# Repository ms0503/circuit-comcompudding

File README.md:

ComComPudding
=============

ComComPuddingは「通信」を主軸に設計された汎用基板です。
MCUはSTM32F405RGT6を採用しコンパクトながら素早く処理することができます。

# 使用IC
## MCP2542WFD
高速通信可能なCANトランシーバです。
詳細は[データシート](https://ww1.microchip.com/downloads/aemDocuments/documents/APID/ProductDocuments/DataSheets/MCP2542FD-MCP2542WFD-4WFD-Data-Sheet-DS20005514C.pdf)
をご覧下さい。

## STM32F405RGT6
メインの処理を担当するMCUです。
詳細は[データシート](https://www.st.com/resource/en/datasheet/stm32f405rg.pdf)
及び[リファレンスマニュアル](https://www.stmcu.jp/download/?dlid=51544_jp)
をご覧下さい。

# インターフェース
## CAN
CAN(Control Area Network)向けのポートが1系統、2つ搭載されており、CANへのアクセス、
5V電源の供給を行うことが出来ます。
### 信号レベル
- マイコン側：3.3V
- 端子側：5V

### マイコンピン
TX：PA11
RX：PA12

## I²C
I²C(Inter-Intergrated Circuit)向けのポートが1系統、1つ搭載されており、I²Cへのアクセス、
5V電源の供給を行うことが出来ます。
### 信号レベル
3.3V
### マイコンピン
I2C1\_SCL：PB6
I2C1\_SDA：PB7

## LED
基板表面に実装された4つのLEDで簡易的な状態表示を行うことが出来ます。
### 信号レベル
3.3V
### マイコンピン
LED1：PB12
LED2：PB13
LED3：PB14
LED4：PB15

## SPI
SPI(Serial Peripheral Interface)向けのポートが2系統、3つ搭載されており、SlaveとしてのMasterとの通信、
MasterとしてのSlave(最大2台まで)との通信、5V電源の供給を行うことが出来ます。  
SPI1をSlave動作、SPI2をMaster動作とすることを想定しています。
### 信号レベル
3.3V
### マイコンピン
SPI1\_SCK：PA5
SPI1\_MISO：PA6
SPI1\_MOSI：PA7
SPI1\_SS：PA4
SPI2\_SCK：PB10
SPI2\_MISO：PC2
SPI2\_MOSI：PC3
SPI2\_SS\_1：PC0
SPI2\_SS\_2：PC1

## U(S)ART
USART(Universal Synchronous-Asynchronous Receiver and Transmitter)向けのポートが4つ、
UART(Universal Asynchronous Receiver and Transmitter)向けのポートが2つ、計6つ搭載されており、
U(S)ARTデバイスとの通信、5V電源の供給を行うことが出来ます。
### 信号レベル
3.3V
### マイコンピン
USART1\_TX：PA9
USART1\_RX：PA10
USART2\_TX：PA2
USART2\_RX：PA3
USART3\_TX：PC10
USART3\_RX：PB11
UART4\_TX：PA0
UART4\_RX：PA1
UART5\_TX：PC12
UART5\_RX：PD2
USART6\_TX：PC6
USART6\_RX：PC7

# ライブラリ
この基板は一部のシンボル・フットプリントに[kicad-mecha](https://github.com/ms0503/kicad-mecha.git)を使用しています。
別途インポートした上でご利用下さい。

# 設計者
Sora Tonami <[ms0503@outlook.com](mailto:ms0503@outlook.com)>

# ライセンス
この基板のデータは[MITライセンス](LICENSE.md)の下に公開されます。ご自由に改変・再配布して頂いて構いません。

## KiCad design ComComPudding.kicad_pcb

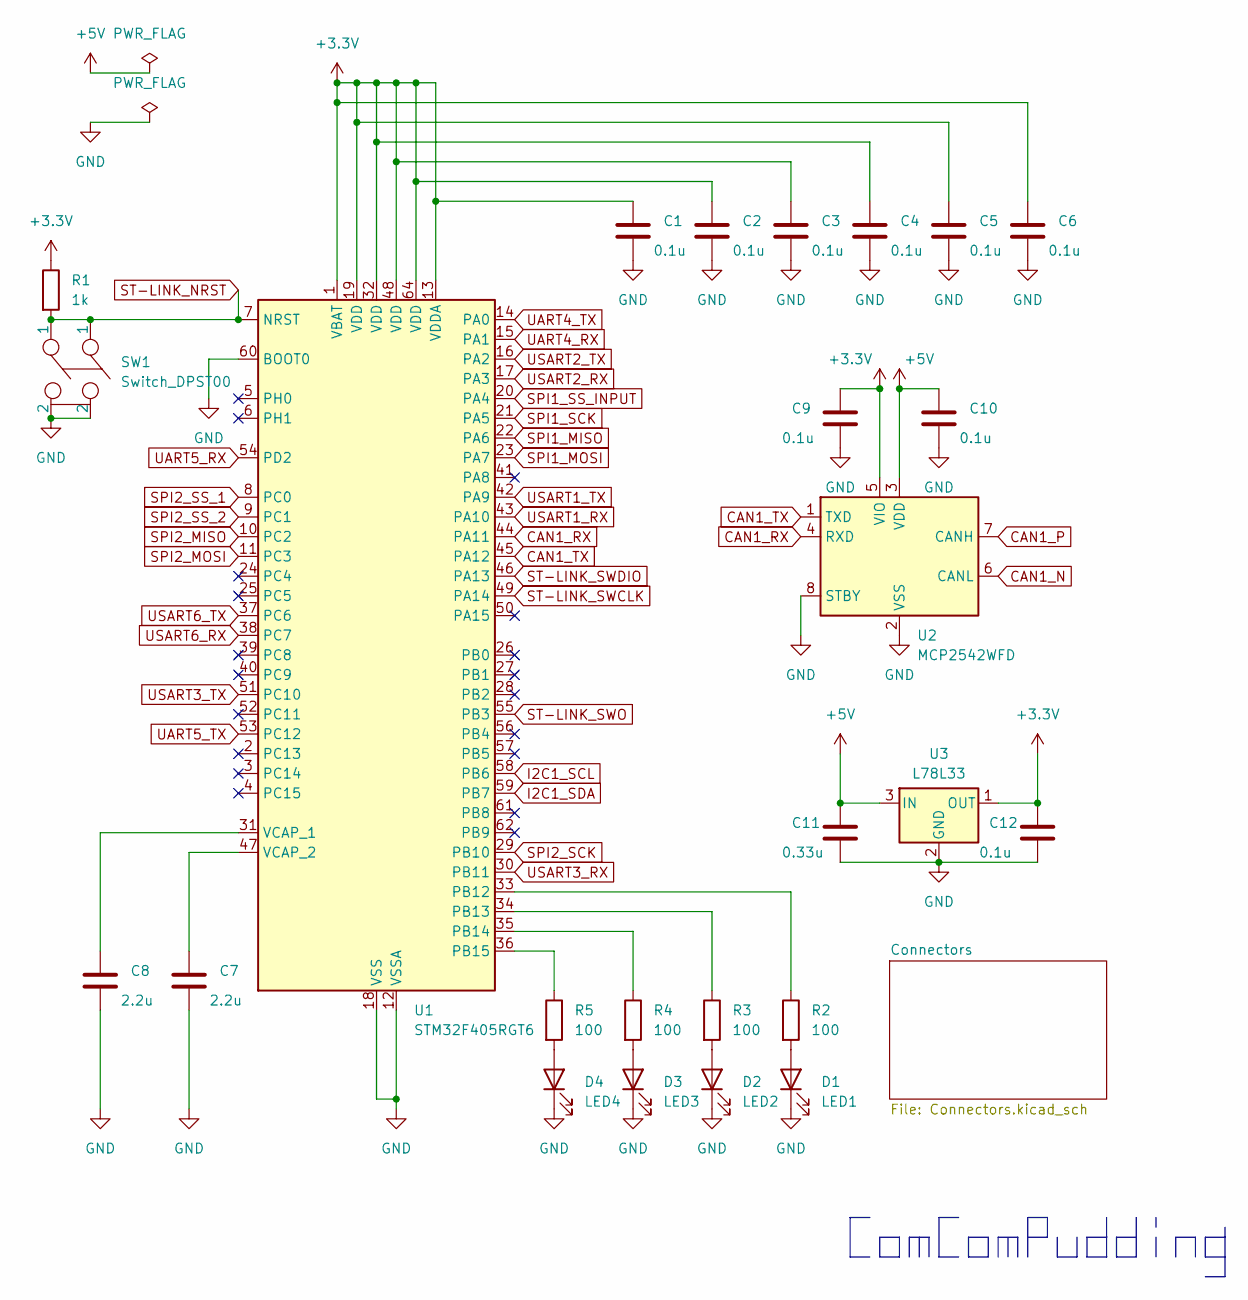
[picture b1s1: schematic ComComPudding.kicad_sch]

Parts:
C1, C2, C3, C4, C5, C6, C9, C10, C12: 0.1u; C_0603_1608Metric
C7, C8: 2.2u; C_0603_1608Metric
C11: 0.33u; C_0603_1608Metric
D1: LED1; LED_0805_2012Metric
D2: LED2; LED_0805_2012Metric
D3: LED3; LED_0805_2012Metric
D4: LED4; LED_0805_2012Metric
R1: 1k; R_0603_1608Metric
R2, R3, R4, R5: 100; R_0603_1608Metric
SW1: Switch_DPST00; SW_Tactile_Straight_KSA0Axx1LFTR
U1: STM32F405RGT6; LQFP-64_10x10mm_P0.5mm
U2: MCP2542WFD; DFN-8-1EP_3x3mm_P0.65mm_EP1.55x2.4mm
U3: L78L33; SOT-89-3

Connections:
+3.3V: C1.1, C2.1, C3.1, C4.1, C5.1, C6.1, C9.1, C12.1, R1.1, U1.1 (VBAT), U1.13 (VDDA), U1.19 (VDD), U1.32 (VDD), U1.48 (VDD), U1.64 (VDD), U2.5 (VIO), U3.1 (OUT); also elsewhere on the board
+5V: C10.1, C11.1, U2.3 (VDD), U3.3 (IN); also elsewhere on the board
CAN1_N: U2.6 (CANL); also elsewhere on the board
CAN1_P: U2.7 (CANH); also elsewhere on the board
CAN1_RX: U1.44 (PA11), U2.4 (RXD)
CAN1_TX: U1.45 (PA12), U2.1 (TXD)
GND: C1.2, C2.2, C3.2, C4.2, C5.2, C6.2, C7.2, C8.2, C9.2, C10.2, C11.2, C12.2, D1.1 (K), D2.1 (K), D3.1 (K), D4.1 (K), SW1.2, U1.12 (VSSA), U1.18 (VSS), U1.60 (BOOT0), U1.63 (VSS), U2.2 (VSS), U2.8 (STBY), U2.9 (VSS), U3.2 (GND); also elsewhere on the board
I2C1_SCL: U1.58 (PB6); also elsewhere on the board
I2C1_SDA: U1.59 (PB7); also elsewhere on the board
unnamed: D1.2 (A), R2.2
unnamed: D2.2 (A), R3.2
unnamed: D3.2 (A), R4.2
unnamed: D4.2 (A), R5.2
unnamed: R2.1, U1.33 (PB12)
unnamed: R3.1, U1.34 (PB13)
unnamed: R4.1, U1.35 (PB14)
unnamed: R5.1, U1.36 (PB15)
unnamed: C8.1, U1.31 (VCAP_1)
unnamed: C7.1, U1.47 (VCAP_2)
SPI1_MISO: U1.22 (PA6); also elsewhere on the board
SPI1_MOSI: U1.23 (PA7); also elsewhere on the board
SPI1_SCK: U1.21 (PA5); also elsewhere on the board
SPI1_SS_INPUT: U1.20 (PA4); also elsewhere on the board
SPI2_MISO: U1.10 (PC2); also elsewhere on the board
SPI2_MOSI: U1.11 (PC3); also elsewhere on the board
SPI2_SCK: U1.29 (PB10); also elsewhere on the board
SPI2_SS_1: U1.8 (PC0); also elsewhere on the board
SPI2_SS_2: U1.9 (PC1); also elsewhere on the board
ST-LINK_NRST: R1.2, SW1.1, U1.7 (NRST); also elsewhere on the board
ST-LINK_SWCLK: U1.49 (PA14); also elsewhere on the board
ST-LINK_SWDIO: U1.46 (PA13); also elsewhere on the board
ST-LINK_SWO: U1.55 (PB3); also elsewhere on the board
UART4_RX: U1.15 (PA1); also elsewhere on the board
UART4_TX: U1.14 (PA0); also elsewhere on the board
UART5_RX: U1.54 (PD2); also elsewhere on the board
UART5_TX: U1.53 (PC12); also elsewhere on the board
USART1_RX: U1.43 (PA10); also elsewhere on the board
USART1_TX: U1.42 (PA9); also elsewhere on the board
USART2_RX: U1.17 (PA3); also elsewhere on the board
USART2_TX: U1.16 (PA2); also elsewhere on the board
USART3_RX: U1.30 (PB11); also elsewhere on the board
USART3_TX: U1.51 (PC10); also elsewhere on the board
USART6_RX: U1.38 (PC7); also elsewhere on the board
USART6_TX: U1.37 (PC6); also elsewhere on the board

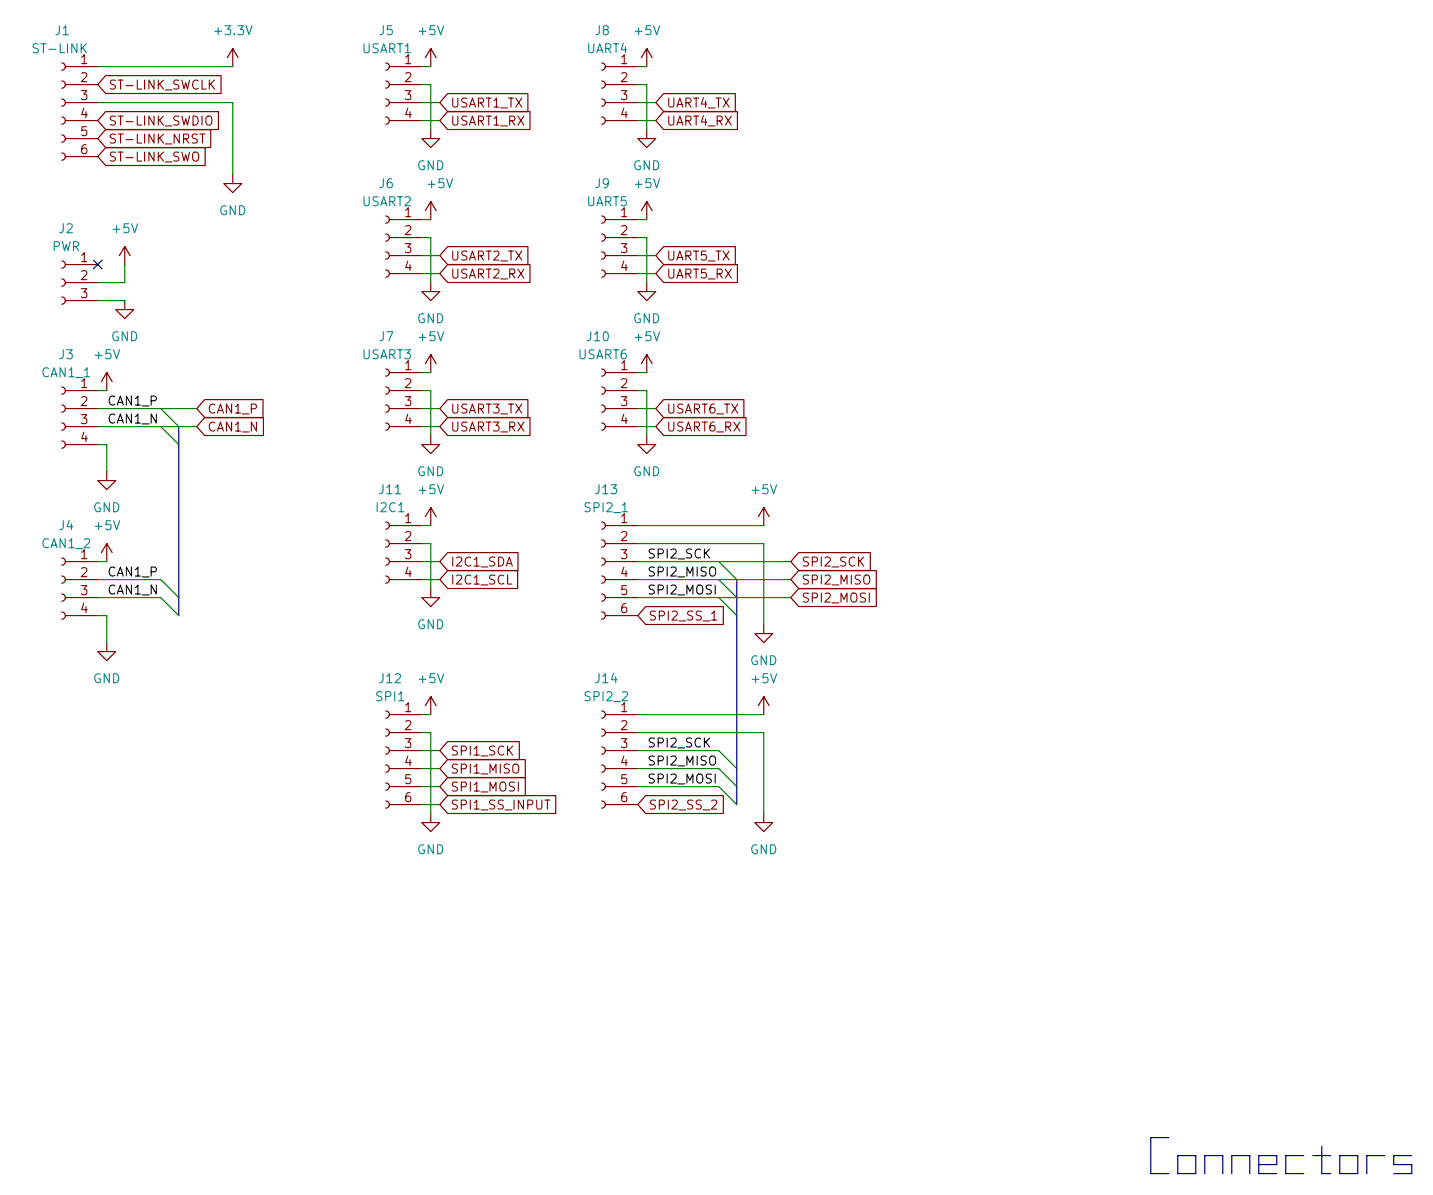
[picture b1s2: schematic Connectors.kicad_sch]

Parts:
J1: ST-LINK; ZH_6pin_Straight
J2: PWR; JST_XH_B3B-XH-A_1x03_P2.50mm_Vertical
J3: CAN1_1; XA_4pin_Straight
J4: CAN1_2; XA_4pin_Straight
J5: USART1; DF1B-4P-2.5DSA
J6: USART2; DF1B-4P-2.5DSA
J7: USART3; DF1B-4P-2.5DSA
J8: UART4; DF1B-4P-2.5DSA
J9: UART5; DF1B-4P-2.5DSA
J10: USART6; DF1B-4P-2.5DSA
J11: I2C1; XA_4pin_Straight
J12: SPI1; XH_Connector_6pin
J13: SPI2_1; XH_Connector_6pin
J14: SPI2_2; XH_Connector_6pin

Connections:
+3.3V: J1.1; also elsewhere on the board
+5V: J2.2, J3.1, J4.1, J5.1, J6.1, J7.1, J8.1, J9.1, J10.1, J11.1, J12.1, J13.1, J14.1; also elsewhere on the board
CAN1_N: J3.3, J4.3; also elsewhere on the board
CAN1_P: J3.2, J4.2; also elsewhere on the board
GND: J1.3, J2.3, J3.4, J4.4, J5.2, J6.2, J7.2, J8.2, J9.2, J10.2, J11.2, J12.2, J13.2, J14.2; also elsewhere on the board
I2C1_SCL: J11.4; also elsewhere on the board
I2C1_SDA: J11.3; also elsewhere on the board
SPI1_MISO: J12.4; also elsewhere on the board
SPI1_MOSI: J12.5; also elsewhere on the board
SPI1_SCK: J12.3; also elsewhere on the board
SPI1_SS_INPUT: J12.6; also elsewhere on the board
SPI2_MISO: J13.4, J14.4; also elsewhere on the board
SPI2_MOSI: J13.5, J14.5; also elsewhere on the board
SPI2_SCK: J13.3, J14.3; also elsewhere on the board
SPI2_SS_1: J13.6; also elsewhere on the board
SPI2_SS_2: J14.6; also elsewhere on the board
ST-LINK_NRST: J1.5; also elsewhere on the board
ST-LINK_SWCLK: J1.2; also elsewhere on the board
ST-LINK_SWDIO: J1.4; also elsewhere on the board
ST-LINK_SWO: J1.6; also elsewhere on the board
UART4_RX: J8.4; also elsewhere on the board
UART4_TX: J8.3; also elsewhere on the board
UART5_RX: J9.4; also elsewhere on the board
UART5_TX: J9.3; also elsewhere on the board
USART1_RX: J5.4; also elsewhere on the board
USART1_TX: J5.3; also elsewhere on the board
USART2_RX: J6.4; also elsewhere on the board
USART2_TX: J6.3; also elsewhere on the board
USART3_RX: J7.4; also elsewhere on the board
USART3_TX: J7.3; also elsewhere on the board
USART6_RX: J10.4; also elsewhere on the board
USART6_TX: J10.3; also elsewhere on the board

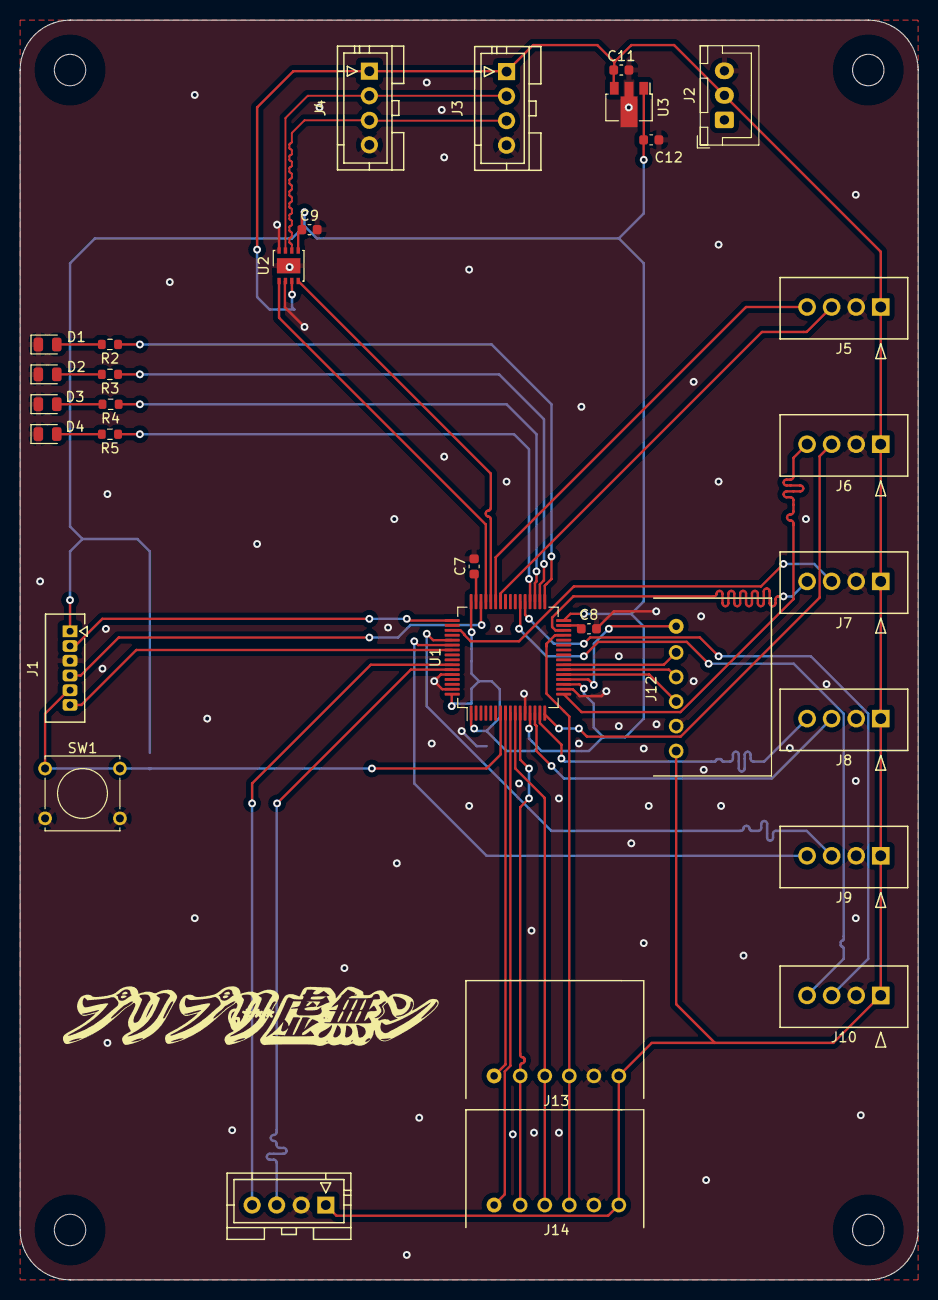
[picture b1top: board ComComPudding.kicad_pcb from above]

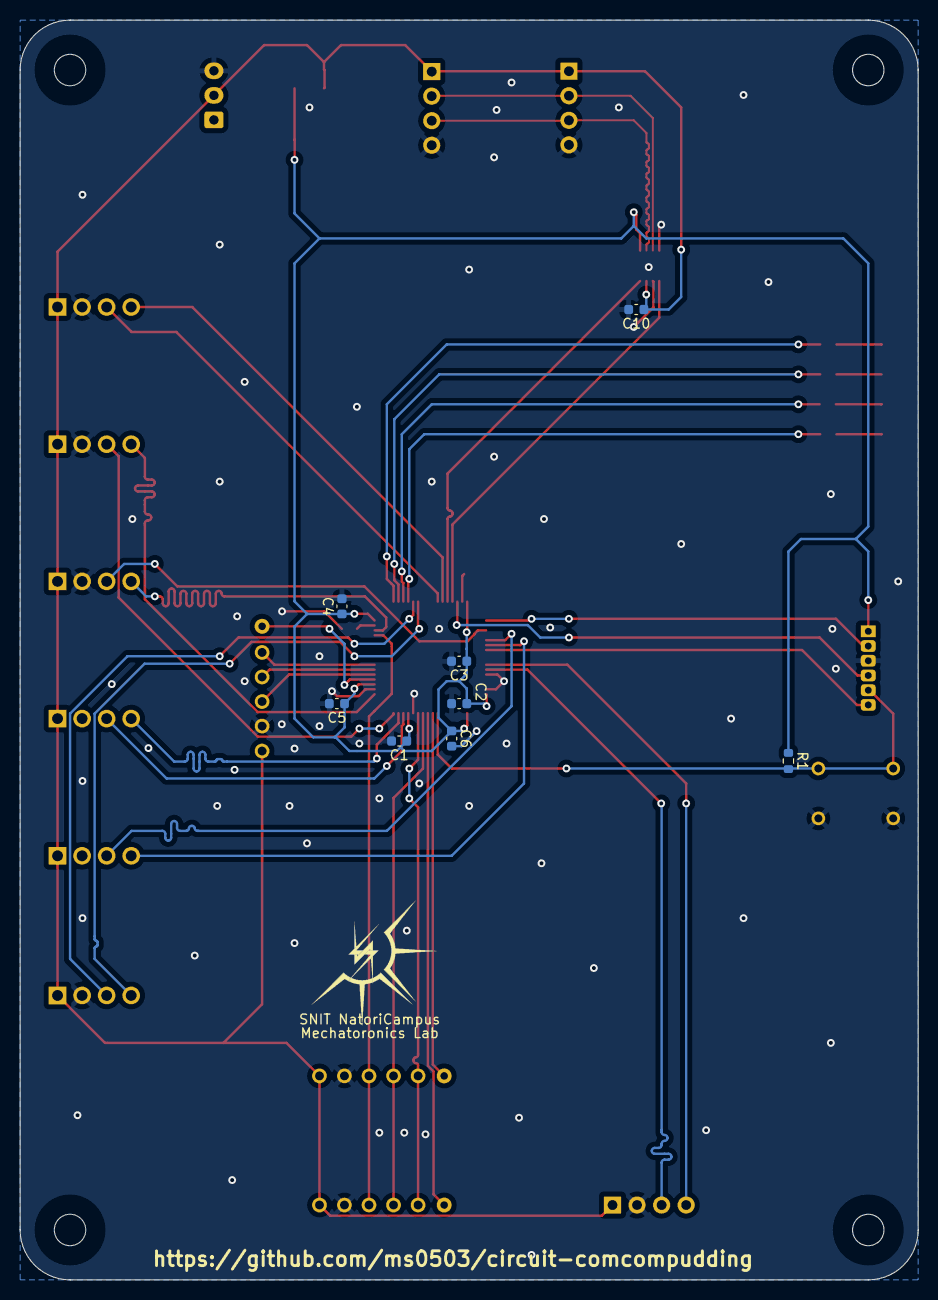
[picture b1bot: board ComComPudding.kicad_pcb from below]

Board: 2 copper layers, 91.4 x 128.3 mm, 43 parts (8 on the bottom side), 44 nets.

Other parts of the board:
 : holeφ3.2
 #2,  #3,  #4: holeφ3.2
